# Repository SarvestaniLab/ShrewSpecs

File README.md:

# ShrewSpecs
A headset-based real-time eye-tracker and VR system for free-walking tree shrews and rats. Currently a work in progress!

## Description of Contents
### 3D designs
3D CAD parts required to assemble the miniature headset.

### PCBs
Eagle project and zipped Gerber files for custom circuit boards to connect to a Raspberry Pi (for power and for future VR capabilities) and to connect various components (cameras, IMU, displays) on the miniature headset. (BOM to be added)

### Arduino
Arduino code for the Giga R1 board used to acquire and decode images CVBS-based cameras as well as orientation and acceleration data from the BNO055 IMU, and do real-time data streaming over high-speed USB-C. (Real-time pupil tracking to be added)

### Matlab
Collection of Matlab scripts used to acquire real-time headset and motion capture data. (Analysis scripts to be added)

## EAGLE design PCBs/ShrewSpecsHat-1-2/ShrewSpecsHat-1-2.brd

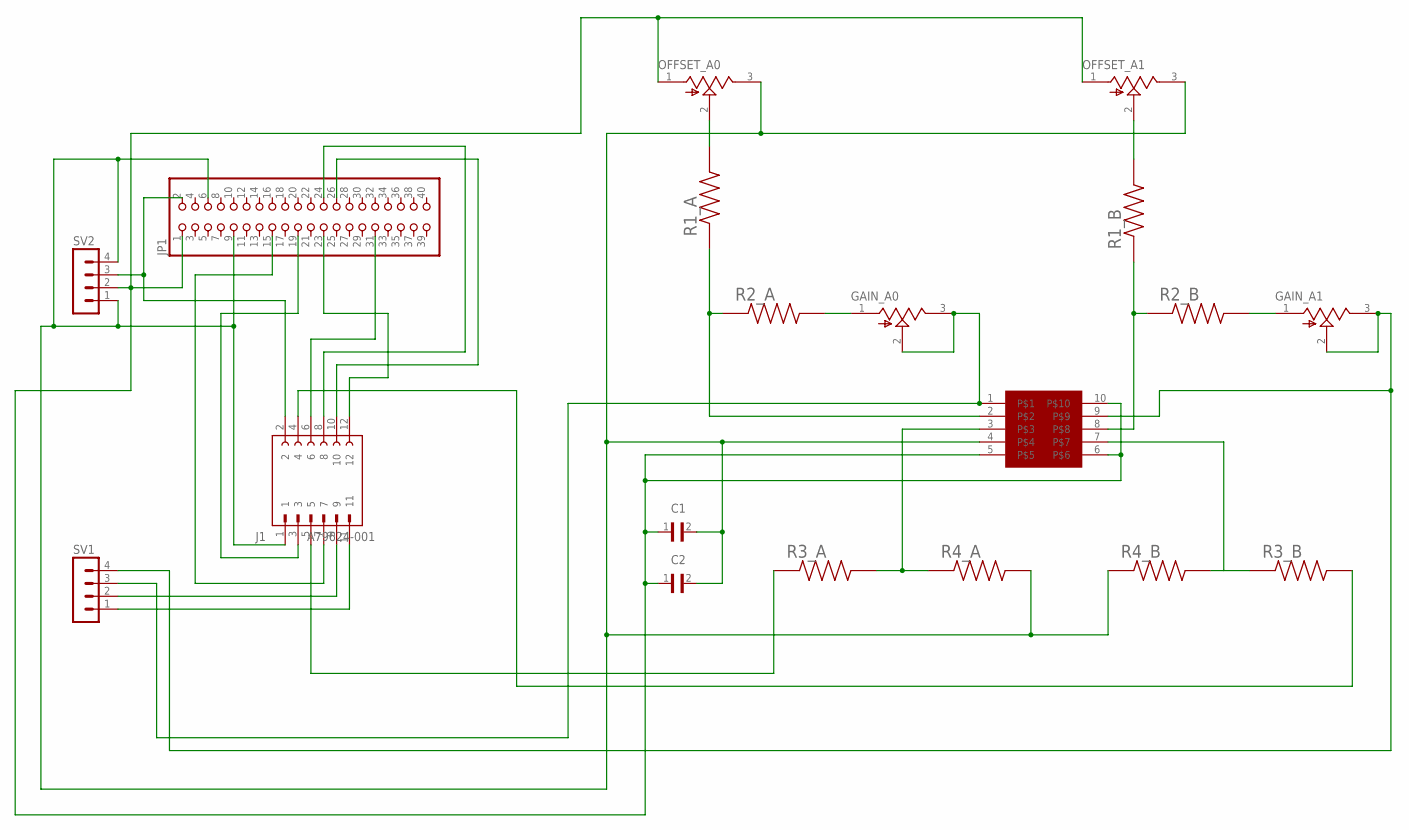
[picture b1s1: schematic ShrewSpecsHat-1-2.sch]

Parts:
C1, C2: CL21A106KOQNNNE; CAPC2012X140N
GAIN_A0, GAIN_A1: 3362P-1-203LF; TRIM_3362P-1-203LF
J1: A79624-001; OMNETICS_A79624-001
JP1: PINHD-2X20-BIG; 2X20-BIG
OFFSET_A0, OFFSET_A1: 3362P-1-203LF; TRIM_3362P-1-203LF
R1_A, R1_B, R2_A, R2_B, R3_A, R3_B, R4_A, R4_B: RC0805FR-07100RL; RESC2012X60N
SV1, SV2: MA04-1
U$1: SOP50P490X110-10N

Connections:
unnamed: C1.1, C2.1, JP1.1, OFFSET_A0.1 (CCW), OFFSET_A1.1 (CCW), SV2.2, U$1.5, U$1.6, U$1.10
unnamed: J1.4, R3_B.2
unnamed: J1.6, JP1.31
unnamed: J1.12, JP1.23
unnamed: J1.8, JP1.24
unnamed: J1.10, JP1.26
unnamed: J1.3, JP1.19
unnamed: J1.5, R3_A.1
unnamed: J1.7, JP1.15
unnamed: J1.9, SV1.2
unnamed: J1.11, SV1.1
unnamed: J1.2, JP1.2, SV2.3
unnamed: GAIN_A0.2 (WIPER), GAIN_A0.3 (CW), SV1.3, U$1.1
unnamed: GAIN_A1.2 (WIPER), GAIN_A1.3 (CW), SV1.4, U$1.9
unnamed: GAIN_A1.1 (CCW), R2_B.2
unnamed: R1_B.1, R2_B.1, U$1.8
unnamed: OFFSET_A1.2 (WIPER), R1_B.2
unnamed: OFFSET_A0.2 (WIPER), R1_A.2
unnamed: R1_A.1, R2_A.1, U$1.2
unnamed: GAIN_A0.1 (CCW), R2_A.2
unnamed: R3_A.2, R4_A.1, U$1.3
unnamed: R3_B.1, R4_B.2, U$1.7
unnamed: C1.2, C2.2, J1.1, JP1.6, JP1.9, OFFSET_A0.3 (CW), OFFSET_A1.3 (CW), R4_A.2, R4_B.1, SV2.1, SV2.4, U$1.4

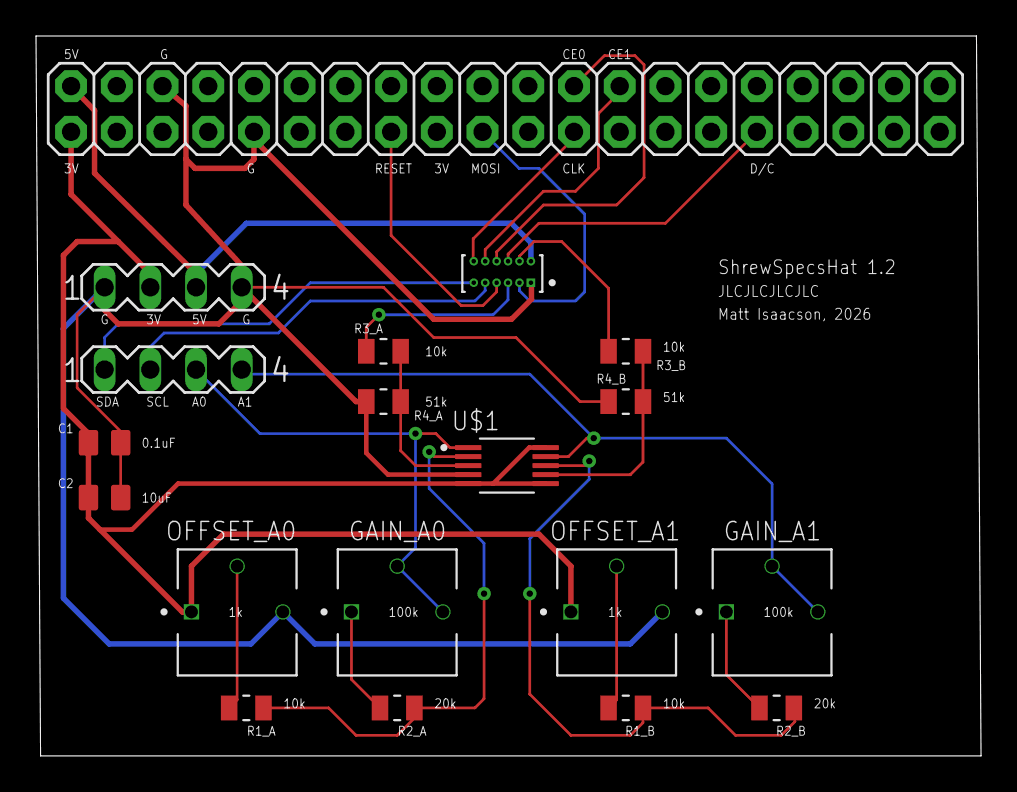
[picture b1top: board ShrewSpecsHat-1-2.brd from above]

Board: 2 copper layers, 52.5 x 40.0 mm, 19 parts (0 on the bottom side), 23 nets.

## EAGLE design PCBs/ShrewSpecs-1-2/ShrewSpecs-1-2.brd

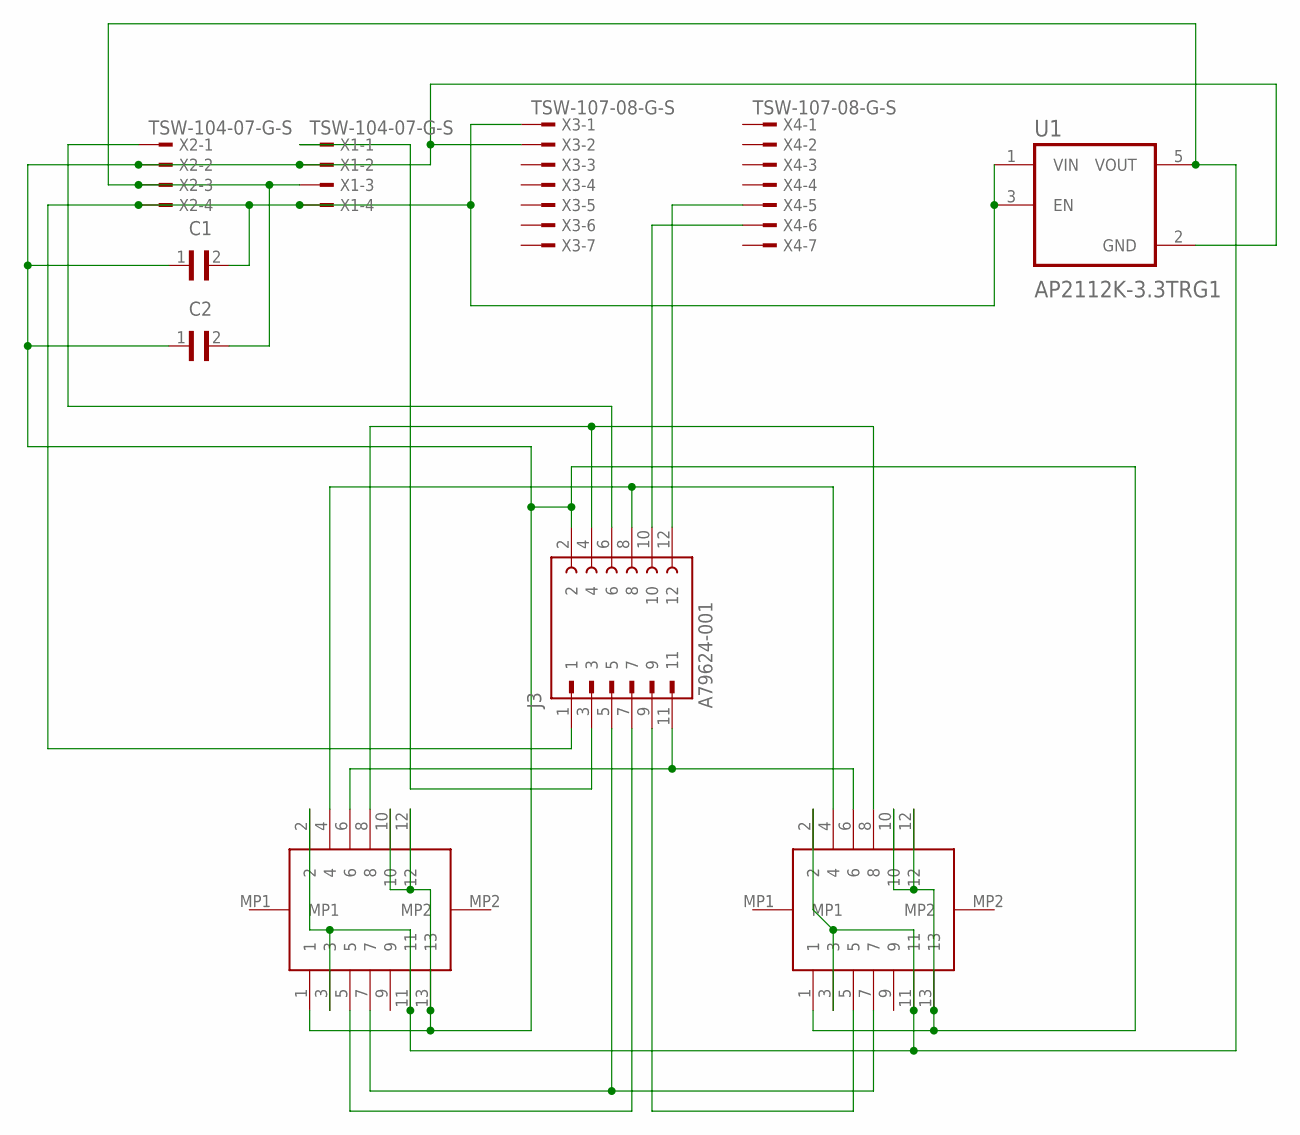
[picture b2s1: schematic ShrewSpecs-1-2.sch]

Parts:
C1, C2: CL21A106KOQNNNE; CAPC2012X140N
J1, J2: 1-2328724-3; 123287243
J3: A79624-001; OMNETICS_A79624-001
U1: AP2112K-3.3TRG1; SOT95P285X140-5N
X1, X2: TSW-104-07-G-S; TSW-104-XX-G-S
X3, X4: TSW-107-08-G-S; TSW-107-XX-G-S

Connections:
unnamed: C1.2, J3.1, U1.1 (VIN), U1.3 (EN), X1.4, X2.4, X3.1
unnamed: J3.6, X2.1
unnamed: C1.1, C2.1, J1.1, J1.10, J1.12, J1.13, J2.1, J2.10, J2.12, J2.13, J3.2, U1.2 (GND), X1.2, X2.2, X3.2
unnamed: J1.7, J2.7, J3.5
unnamed: J1.5, J3.7
unnamed: J2.5, J3.9
unnamed: J1.6, J2.6, J3.11
unnamed: J1.8, J2.8, J3.4
unnamed: J1.4, J2.4, J3.8
unnamed: J3.3, X1.1
unnamed: J3.12, X4.5
unnamed: J3.10, X4.6
unnamed: C2.2, J1.2, J1.3, J1.11, J2.2, J2.3, J2.11, U1.5 (VOUT), X1.3, X2.3

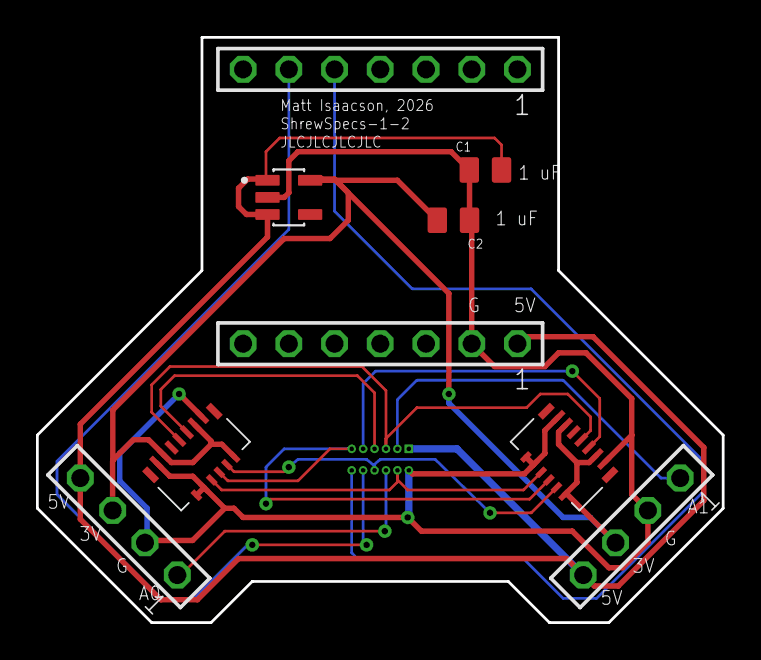
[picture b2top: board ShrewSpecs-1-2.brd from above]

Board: 2 copper layers, 38.1 x 32.5 mm, 10 parts (1 on the bottom side), 13 nets.
